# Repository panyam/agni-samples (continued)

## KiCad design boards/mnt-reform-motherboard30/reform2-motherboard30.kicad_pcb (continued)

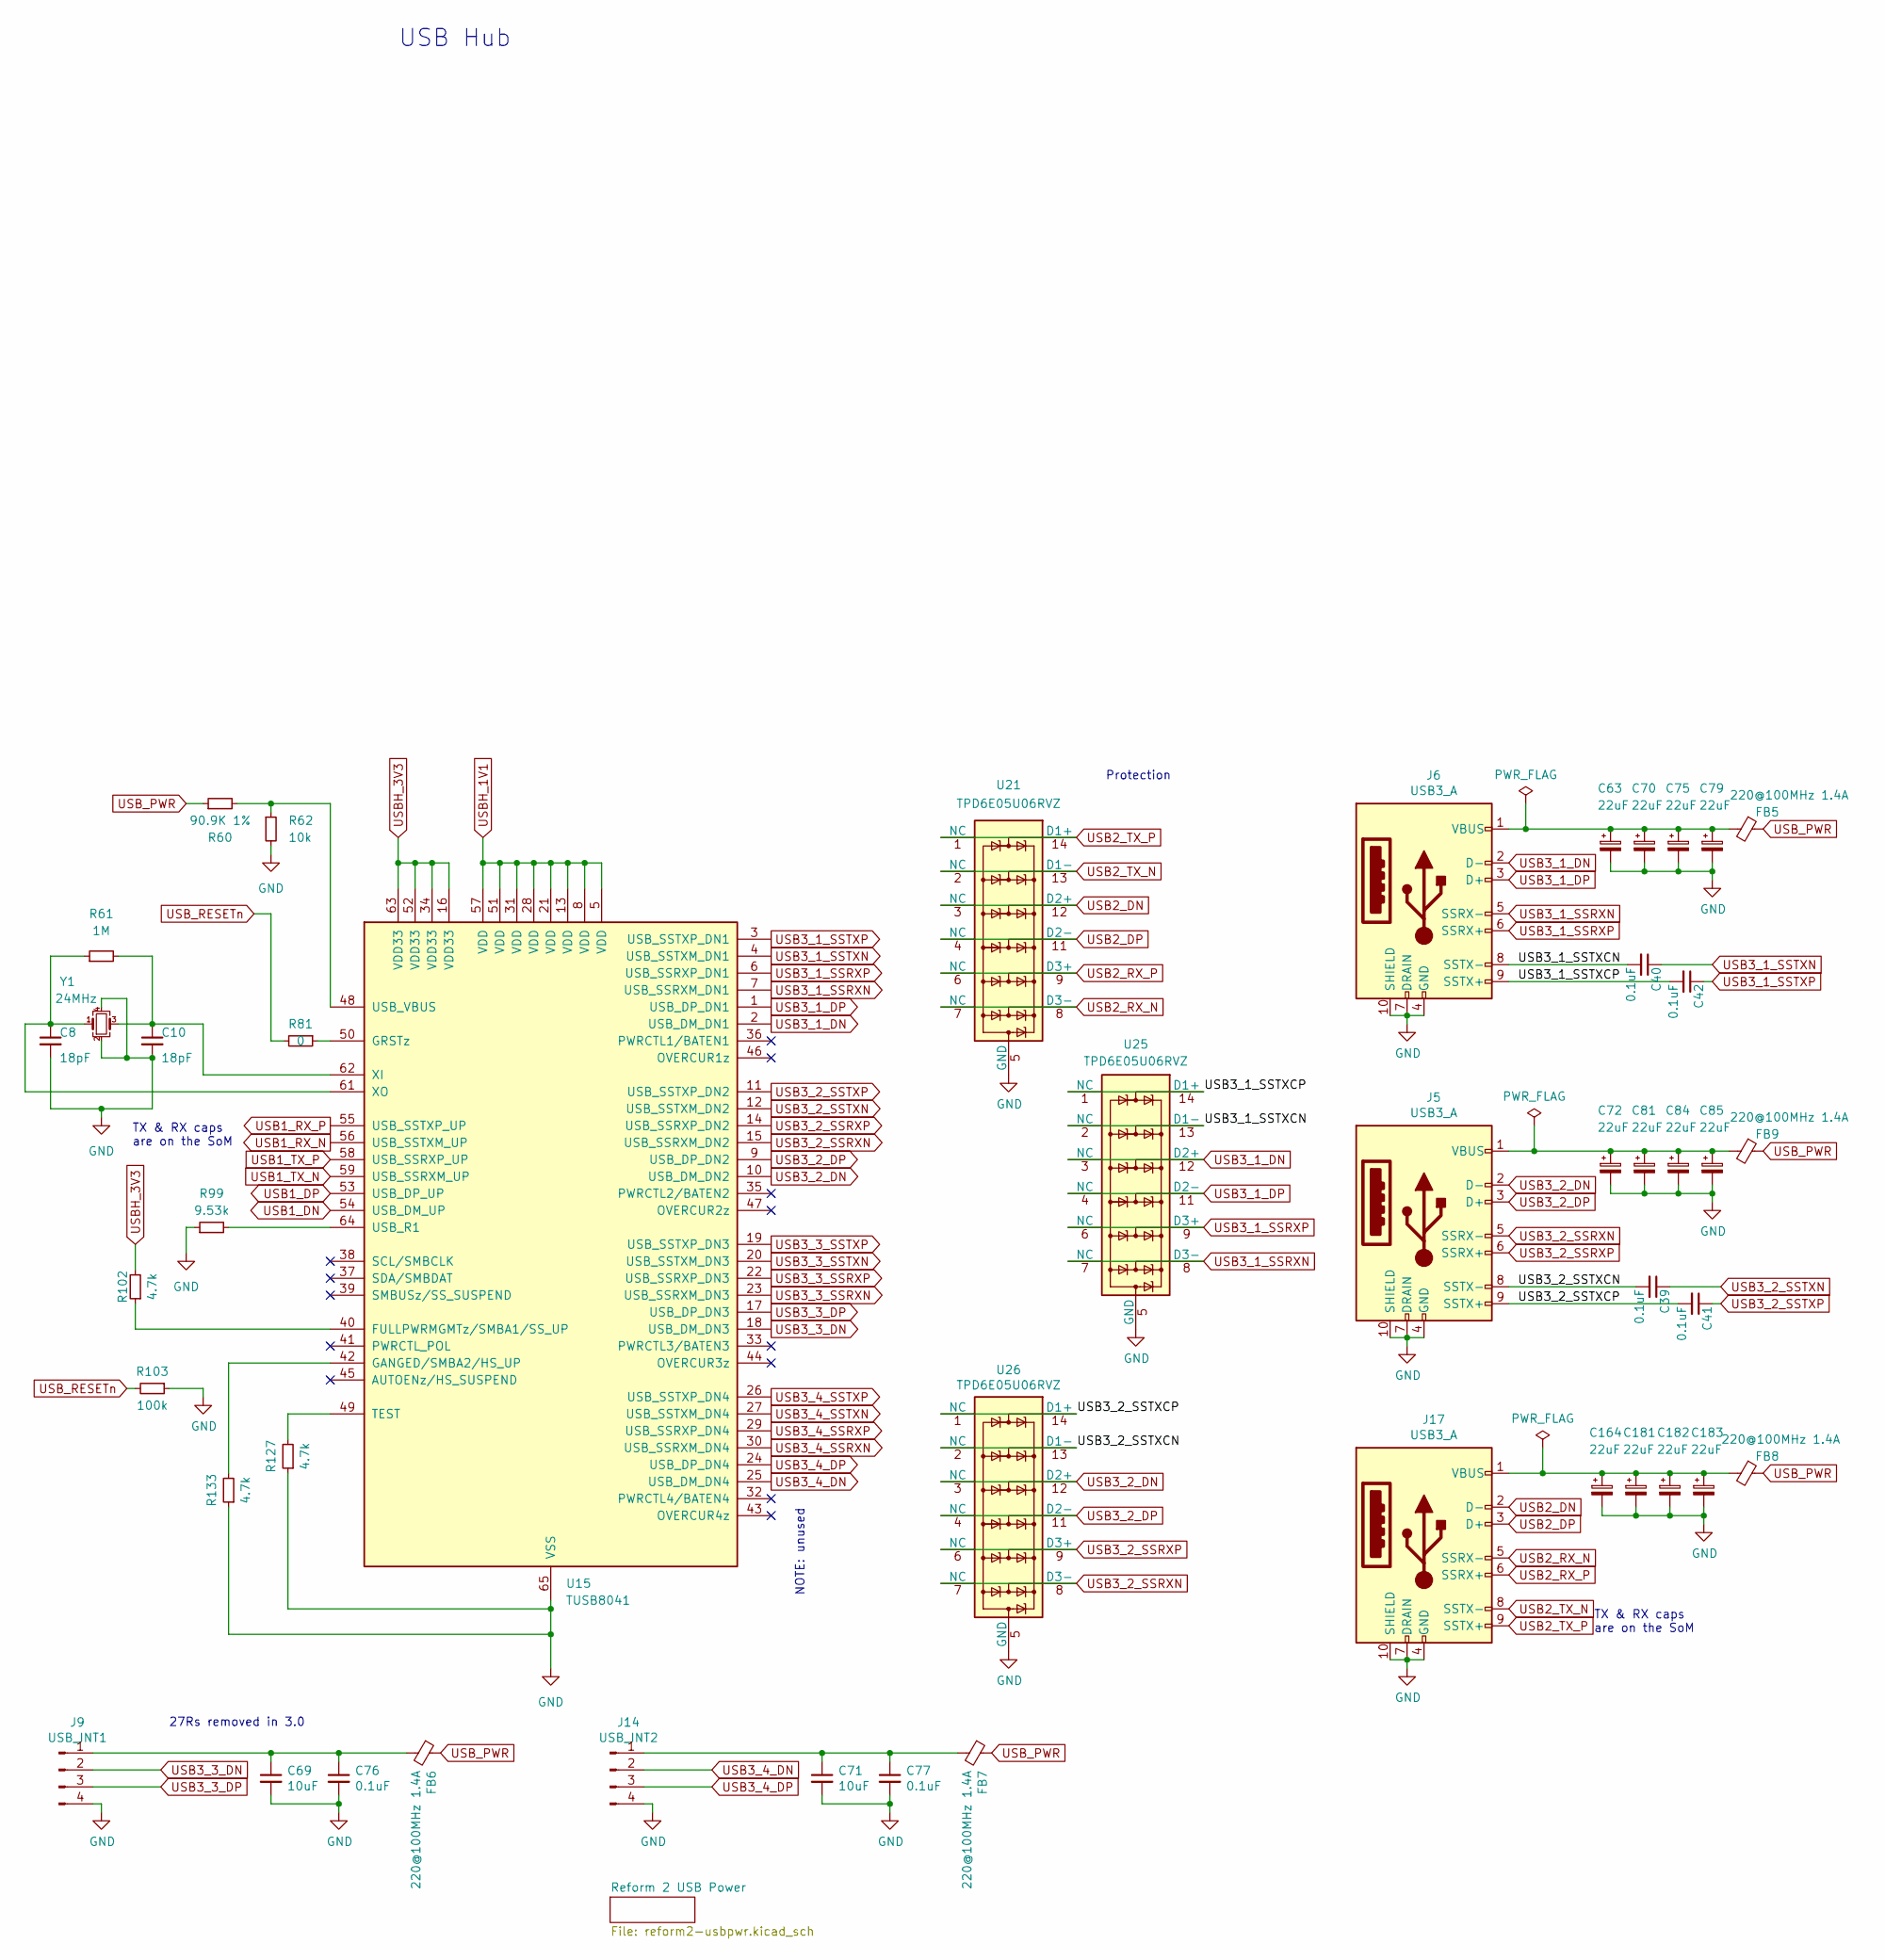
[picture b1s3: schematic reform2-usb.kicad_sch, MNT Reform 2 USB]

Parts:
C8, C10: 18pF; C_0603_1608Metric; LCSC C107040
C39, C40, C41, C42, C76, C77: 0.1uF; C_0603_1608Metric
C63, C70, C72, C75, C79, C81, C84, C85, C164, C181, C182, C183: 22uF; C_0603_1608Metric; LCSC C140782
C69, C71: 10uF; C_0603_1608Metric
FB5, FB6, FB7, FB8, FB9: 220@100MHz 1.4A; L_0603_1608Metric
J5, J6, J17: USB3_A; 692121030100
J9: USB_INT1; JST_PH_B4B-PH-K_1x04_P2.00mm_Vertical
J14: USB_INT2; JST_PH_B4B-PH-K_1x04_P2.00mm_Vertical
R60: 90.9K 1%; R_0603_1608Metric
R61: 1M; R_0603_1608Metric
R62: 10k; R_0603_1608Metric
R81: 0; R_0603_1608Metric
R99: 9.53k; R_0603_1608Metric; LCSC C321660
R102: 4.7k; R_0603_1608Metric; LCSC C105871
R103: 100k; R_0603_1608Metric
R127, R133: 4.7k; R_0603_1608Metric
U15: TUSB8041; QFN-64-1EP_9x9mm_P0.5mm_EP6x6mm_ThermalVias
U21, U25, U26: TPD6E05U06RVZ; Texas_R-PUSON-N14
Y1: 24MHz; Crystal_SMD_Abracon_ABM8G-4Pin_3.2x2.5mm; LCSC C91744

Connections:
/Reform 2 USB/USB3_1_SSTXCN: C40.2, J6.8 (SSTX-), U25.2 (NC), U25.13 (D1-)
/Reform 2 USB/USB3_1_SSTXCP: C42.2, J6.9 (SSTX+), U25.1 (NC), U25.14 (D1+)
/Reform 2 USB/USB3_2_SSTXCN: C39.2, J5.8 (SSTX-), U26.2 (NC), U26.13 (D1-)
/Reform 2 USB/USB3_2_SSTXCP: C41.2, J5.9 (SSTX+), U26.1 (NC), U26.14 (D1+)
GND: C8.2, C10.2, C63.2, C69.2, C70.2, C71.2, C72.2, C75.2, C76.2, C77.2, C79.2, C81.2, C84.2, C85.2, C164.2, C181.2, C182.2, C183.2, J5.4 (GND), J5.7 (DRAIN), J5.10 (SHIELD), J6.4 (GND), J6.7 (DRAIN), J6.10 (SHIELD), J9.4, J14.4, J17.4 (GND), J17.7 (DRAIN), J17.10 (SHIELD), R62.2, R99.1, R103.1, R127.1, R133.1, U15.65 (VSS), U21.5 (GND), U21.10 (GND), U25.5 (GND), U25.10 (GND), U26.5 (GND), U26.10 (GND), Y1.2, Y1.4; also elsewhere on the board
unnamed: C72.1, C81.1, C84.1, C85.1, FB9.2, J5.1 (VBUS)
unnamed: C63.1, C70.1, C75.1, C79.1, FB5.2, J6.1 (VBUS)
unnamed: C69.1, C76.1, FB6.2, J9.1
unnamed: C71.1, C77.1, FB7.2, J14.1
unnamed: C164.1, C181.1, C182.1, C183.1, FB8.2, J17.1 (VBUS)
unnamed: R102.1, U15.40 (FULLPWRMGMTz/SMBA1/SS_UP)
unnamed: R133.2, U15.42 (GANGED/SMBA2/HS_UP)
unnamed: R81.1, U15.50 (GRSTz)
unnamed: R127.2, U15.49 (TEST)
unnamed: R99.2, U15.64 (USB_R1)
unnamed: R60.2, R62.1, U15.48 (USB_VBUS)
unnamed: C10.1, R61.2, U15.62 (XI), Y1.3
unnamed: C8.1, R61.1, U15.61 (XO), Y1.1
USB1_DN: U15.54 (USB_DM_UP); also elsewhere on the board
USB1_DP: U15.53 (USB_DP_UP); also elsewhere on the board
USB1_RX_N: U15.56 (USB_SSTXM_UP); also elsewhere on the board
USB1_RX_P: U15.55 (USB_SSTXP_UP); also elsewhere on the board
USB1_TX_N: U15.59 (USB_SSRXM_UP); also elsewhere on the board
USB1_TX_P: U15.58 (USB_SSRXP_UP); also elsewhere on the board
USB2_DN: J17.2 (D-), U21.3 (NC), U21.12 (D2+); also elsewhere on the board
USB2_DP: J17.3 (D+), U21.4 (NC), U21.11 (D2-); also elsewhere on the board
USB2_RX_N: J17.5 (SSRX-), U21.7 (NC), U21.8 (D3-); also elsewhere on the board
USB2_RX_P: J17.6 (SSRX+), U21.6 (NC), U21.9 (D3+); also elsewhere on the board
USB2_TX_N: J17.8 (SSTX-), U21.2 (NC), U21.13 (D1-); also elsewhere on the board
USB2_TX_P: J17.9 (SSTX+), U21.1 (NC), U21.14 (D1+); also elsewhere on the board
USB3_1_DN: J6.2 (D-), U15.2 (USB_DM_DN1), U25.3 (NC), U25.12 (D2+)
USB3_1_DP: J6.3 (D+), U15.1 (USB_DP_DN1), U25.4 (NC), U25.11 (D2-)
USB3_1_SSRXN: J6.5 (SSRX-), U15.7 (USB_SSRXM_DN1), U25.7 (NC), U25.8 (D3-)
USB3_1_SSRXP: J6.6 (SSRX+), U15.6 (USB_SSRXP_DN1), U25.6 (NC), U25.9 (D3+)
USB3_1_SSTXN: C40.1, U15.4 (USB_SSTXM_DN1)
USB3_1_SSTXP: C42.1, U15.3 (USB_SSTXP_DN1)
USB3_2_DN: J5.2 (D-), U15.10 (USB_DM_DN2), U26.3 (NC), U26.12 (D2+)
USB3_2_DP: J5.3 (D+), U15.9 (USB_DP_DN2), U26.4 (NC), U26.11 (D2-)
USB3_2_SSRXN: J5.5 (SSRX-), U15.15 (USB_SSRXM_DN2), U26.7 (NC), U26.8 (D3-)
USB3_2_SSRXP: J5.6 (SSRX+), U15.14 (USB_SSRXP_DN2), U26.6 (NC), U26.9 (D3+)
USB3_2_SSTXN: C39.1, U15.12 (USB_SSTXM_DN2)
USB3_2_SSTXP: C41.1, U15.11 (USB_SSTXP_DN2)
USB3_3_DN: J9.2, U15.18 (USB_DM_DN3)
USB3_3_DP: J9.3, U15.17 (USB_DP_DN3)
USB3_3_SSRXN: U15.23 (USB_SSRXM_DN3)
USB3_3_SSRXP: U15.22 (USB_SSRXP_DN3)
USB3_3_SSTXN: U15.20 (USB_SSTXM_DN3)
USB3_3_SSTXP: U15.19 (USB_SSTXP_DN3)
USB3_4_DN: J14.2, U15.25 (USB_DM_DN4)
USB3_4_DP: J14.3, U15.24 (USB_DP_DN4)
USB3_4_SSRXN: U15.30 (USB_SSRXM_DN4)
USB3_4_SSRXP: U15.29 (USB_SSRXP_DN4)
USB3_4_SSTXN: U15.27 (USB_SSTXM_DN4)
USB3_4_SSTXP: U15.26 (USB_SSTXP_DN4)
USB_PWR: FB5.1, FB6.1, FB7.1, FB8.1, FB9.1, R60.1; also elsewhere on the board
USB_RESETn: R81.2, R103.2; also elsewhere on the board

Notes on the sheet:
USB Hub
TX & RX caps are on the SoM
NOTE: unused
27Rs removed in 3.0
Protection

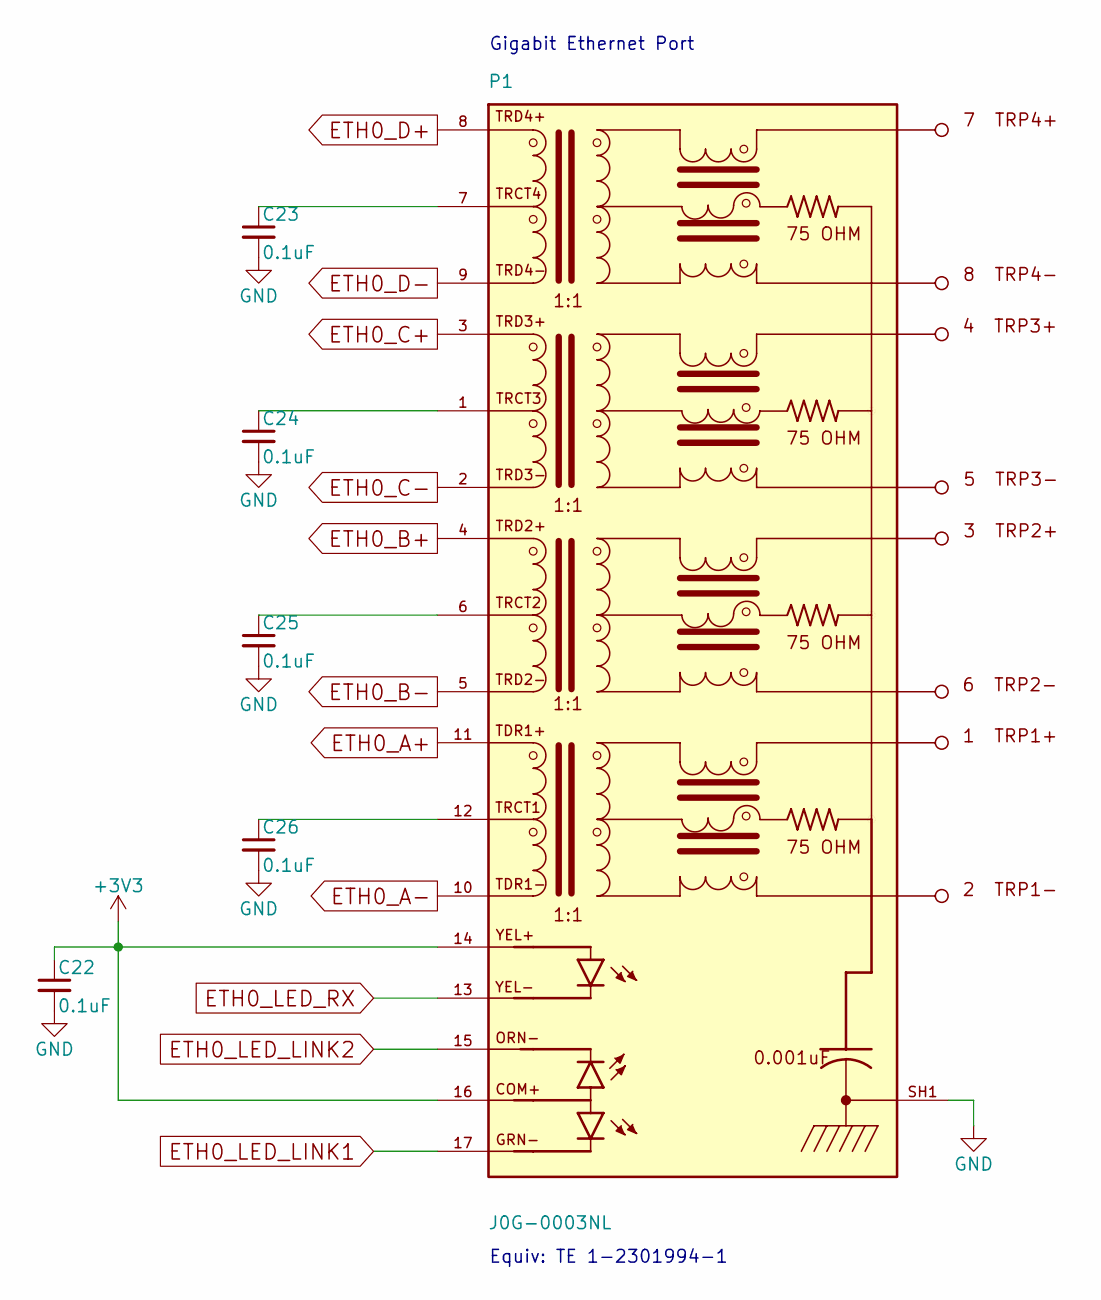
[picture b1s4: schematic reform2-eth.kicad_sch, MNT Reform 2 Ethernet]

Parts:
C22, C23, C24, C25, C26: 0.1uF; C_0603_1608Metric
P1: J0G-0003NL; PULSE_J0G-0003NL

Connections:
+3V3: C22.1, P1.14 (YEL+), P1.16 (COM+); also elsewhere on the board
ETH0_A+: P1.11 (TDR1+); also elsewhere on the board
ETH0_A-: P1.10 (TDR1-); also elsewhere on the board
ETH0_B+: P1.4 (TRD2+); also elsewhere on the board
ETH0_B-: P1.5 (TRD2-); also elsewhere on the board
ETH0_C+: P1.3 (TRD3+); also elsewhere on the board
ETH0_C-: P1.2 (TRD3-); also elsewhere on the board
ETH0_D+: P1.8 (TRD4+); also elsewhere on the board
ETH0_D-: P1.9 (TRD4-); also elsewhere on the board
ETH0_LED_LINK1: P1.17 (GRN-); also elsewhere on the board
ETH0_LED_LINK2: P1.15 (ORN-); also elsewhere on the board
ETH0_LED_RX: P1.13 (YEL-); also elsewhere on the board
GND: C22.2, C23.2, C24.2, C25.2, C26.2, P1.SH1 (SHIELD), P1.SH2 (SHIELD); also elsewhere on the board
unnamed: C26.1, P1.12 (TRCT1)
unnamed: C25.1, P1.6 (TRCT2)
unnamed: C24.1, P1.1 (TRCT3)
unnamed: C23.1, P1.7 (TRCT4)

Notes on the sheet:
Equiv: TE 1-2301994-1
Gigabit Ethernet Port

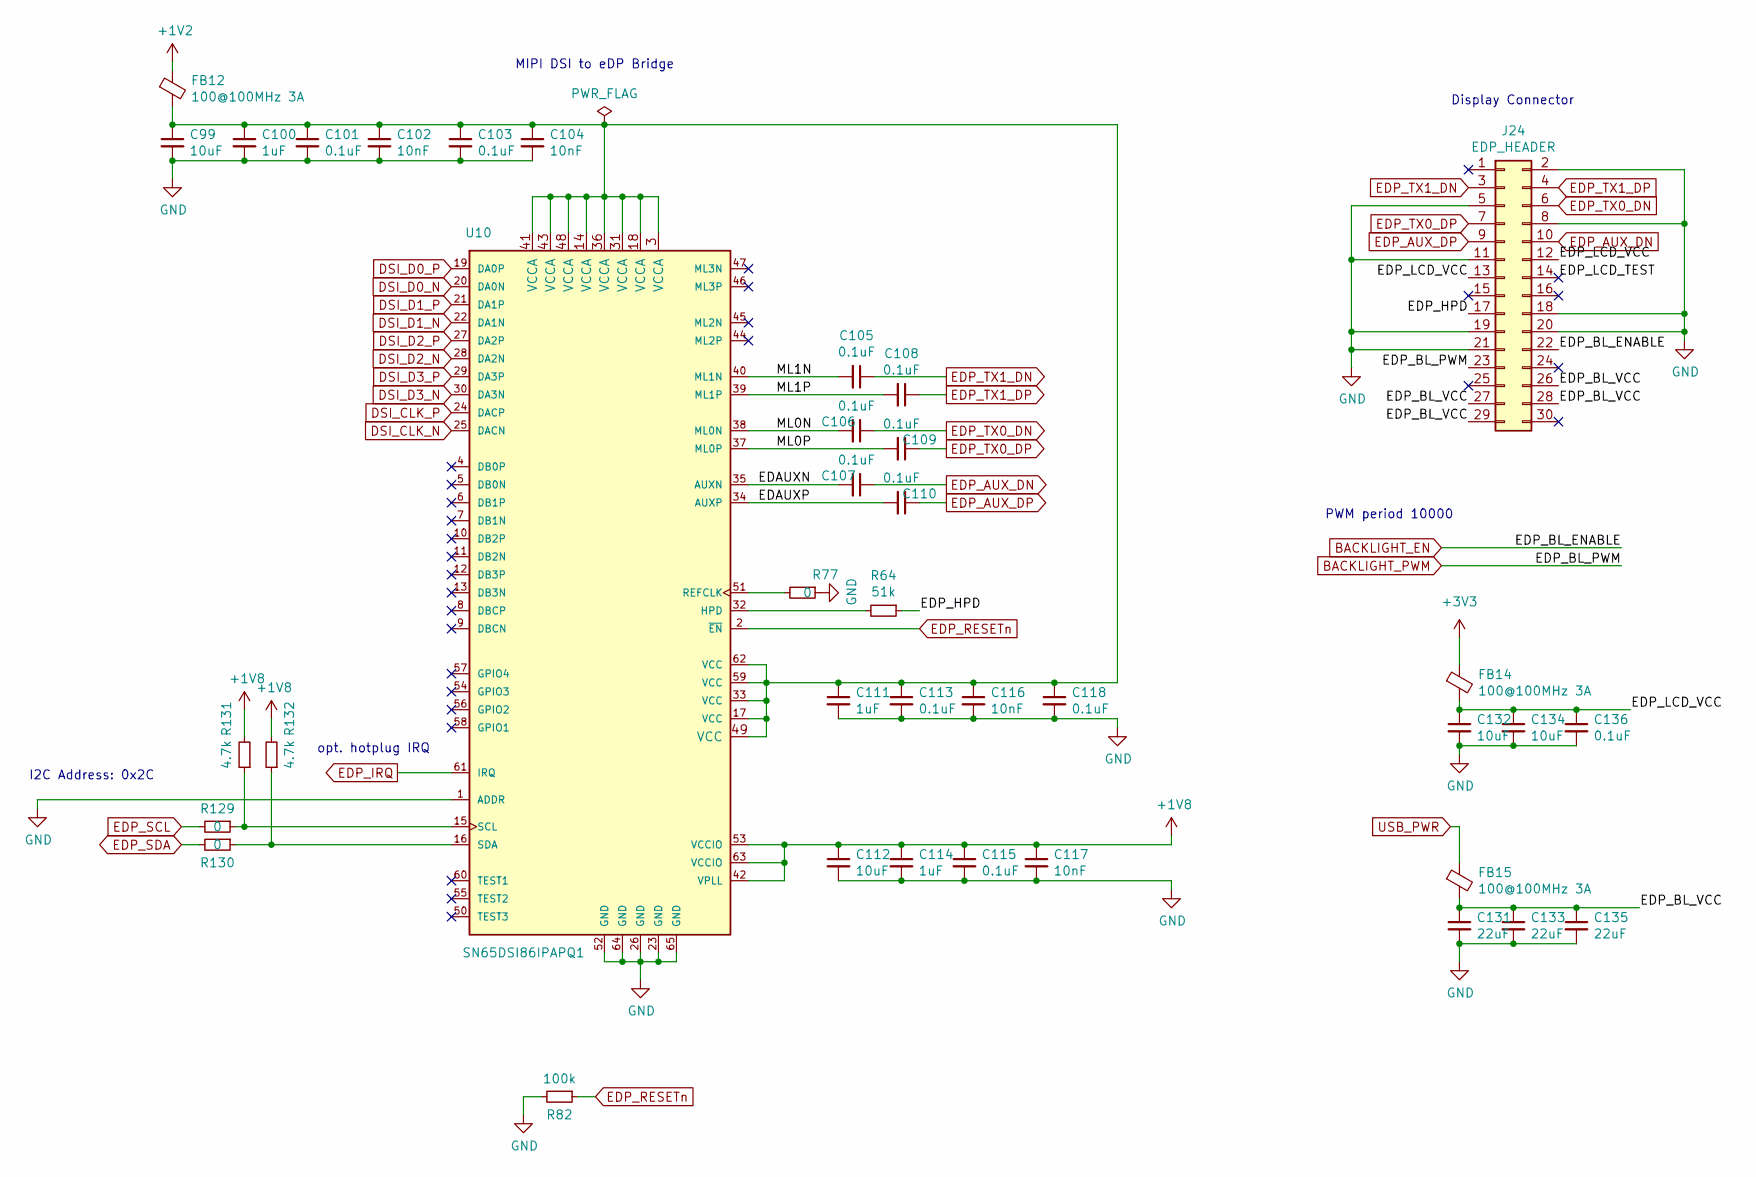
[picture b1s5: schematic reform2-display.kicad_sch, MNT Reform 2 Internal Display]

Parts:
C99, C112, C132, C134: 10uF; C_0603_1608Metric
C100, C111, C114: 1uF; C_0603_1608Metric
C101, C103, C105, C106, C107, C108, C109, C110, C113, C115, C118, C136: 0.1uF; C_0603_1608Metric
C102, C104, C116, C117: 10nF; C_0603_1608Metric
C131, C133, C135: 22uF; C_0603_1608Metric
FB12, FB14, FB15: 100@100MHz 3A; L_0603_1608Metric
J24: EDP_HEADER; PinHeader_2x15_P2.00mm_Vertical
R64: 51k; R_0603_1608Metric
R77, R129, R130: 0; R_0603_1608Metric
R82: 100k; R_0603_1608Metric
R131, R132: 4.7k; R_0603_1608Metric
U10: SN65DSI86IPAPQ1; HTQFP-64-1EP_10x10mm_P0.5mm_EP8x8mm

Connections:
+1V2: FB12.1; also elsewhere on the board
+1V8: C112.1, C114.1, C115.1, C117.1, R131.2, R132.2, U10.42 (VPLL), U10.53 (VCCIO), U10.63 (VCCIO); also elsewhere on the board
+3V3: FB14.1; also elsewhere on the board
/Reform 2 Display/EDAUXN: C107.2, U10.35 (AUXN)
/Reform 2 Display/EDAUXP: C110.2, U10.34 (AUXP)
/Reform 2 Display/EDP_BL_VCC: C131.1, C133.1, C135.1, FB15.2, J24.26, J24.27, J24.28, J24.29
/Reform 2 Display/EDP_HPD: J24.17, R64.1
/Reform 2 Display/EDP_LCD_TEST: J24.14
/Reform 2 Display/EDP_LCD_VCC: C132.1, C134.1, C136.1, FB14.2, J24.12, J24.13
/Reform 2 Display/ML0N: C106.2, U10.38 (ML0N)
/Reform 2 Display/ML0P: C109.2, U10.37 (ML0P)
/Reform 2 Display/ML1N: C105.2, U10.40 (ML1N)
/Reform 2 Display/ML1P: C108.2, U10.39 (ML1P)
BACKLIGHT_EN: J24.22; also elsewhere on the board
BACKLIGHT_PWM: J24.23; also elsewhere on the board
DSI_CLK_N: U10.25 (DACN); also elsewhere on the board
DSI_CLK_P: U10.24 (DACP); also elsewhere on the board
DSI_D0_N: U10.20 (DA0N); also elsewhere on the board
DSI_D0_P: U10.19 (DA0P); also elsewhere on the board
DSI_D1_N: U10.22 (DA1N); also elsewhere on the board
DSI_D1_P: U10.21 (DA1P); also elsewhere on the board
DSI_D2_N: U10.28 (DA2N); also elsewhere on the board
DSI_D2_P: U10.27 (DA2P); also elsewhere on the board
DSI_D3_N: U10.30 (DA3N); also elsewhere on the board
DSI_D3_P: U10.29 (DA3P); also elsewhere on the board
EDP_AUX_DN: C107.1, J24.10
EDP_AUX_DP: C110.1, J24.9
EDP_IRQ: U10.61 (IRQ); also elsewhere on the board
EDP_RESETn: R82.1, U10.2 (~EN); also elsewhere on the board
EDP_SCL: R129.2; also elsewhere on the board
EDP_SDA: R130.2; also elsewhere on the board
EDP_TX0_DN: C106.1, J24.6
EDP_TX0_DP: C109.1, J24.7
EDP_TX1_DN: C105.1, J24.3
EDP_TX1_DP: C108.1, J24.4
GND: C99.2, C100.2, C101.2, C102.2, C103.2, C104.2, C111.2, C112.2, C113.2, C114.2, C115.2, C116.2, C117.2, C118.2, C131.2, C132.2, C133.2, C134.2, C135.2, C136.2, J24.2, J24.5, J24.8, J24.11, J24.18, J24.19, J24.20, J24.21, R77.1, R82.2, U10.1 (ADDR), U10.23 (GND), U10.26 (GND), U10.52 (GND), U10.64 (GND), U10.65 (GND); also elsewhere on the board
unnamed: C99.1, C100.1, C101.1, C102.1, C103.1, C104.1, C111.1, C113.1, C116.1, C118.1, FB12.2, U10.3 (VCCA), U10.14 (VCCA), U10.17 (VCC), U10.18 (VCCA), U10.31 (VCCA), U10.33 (VCC), U10.36 (VCCA), U10.41 (VCCA), U10.43 (VCCA), U10.48 (VCCA), U10.49 (VCC), U10.59 (VCC), U10.62 (VCC)
unnamed: R64.2, U10.32 (HPD)
unnamed: R77.2, U10.51 (REFCLK)
unnamed: R129.1, R131.1, U10.15 (SCL)
unnamed: R130.1, R132.1, U10.16 (SDA)
USB_PWR: FB15.1; also elsewhere on the board

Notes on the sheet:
PWM period 10000
MIPI DSI to eDP Bridge
opt. hotplug IRQ
Display Connector
I2C Address: 0x2C

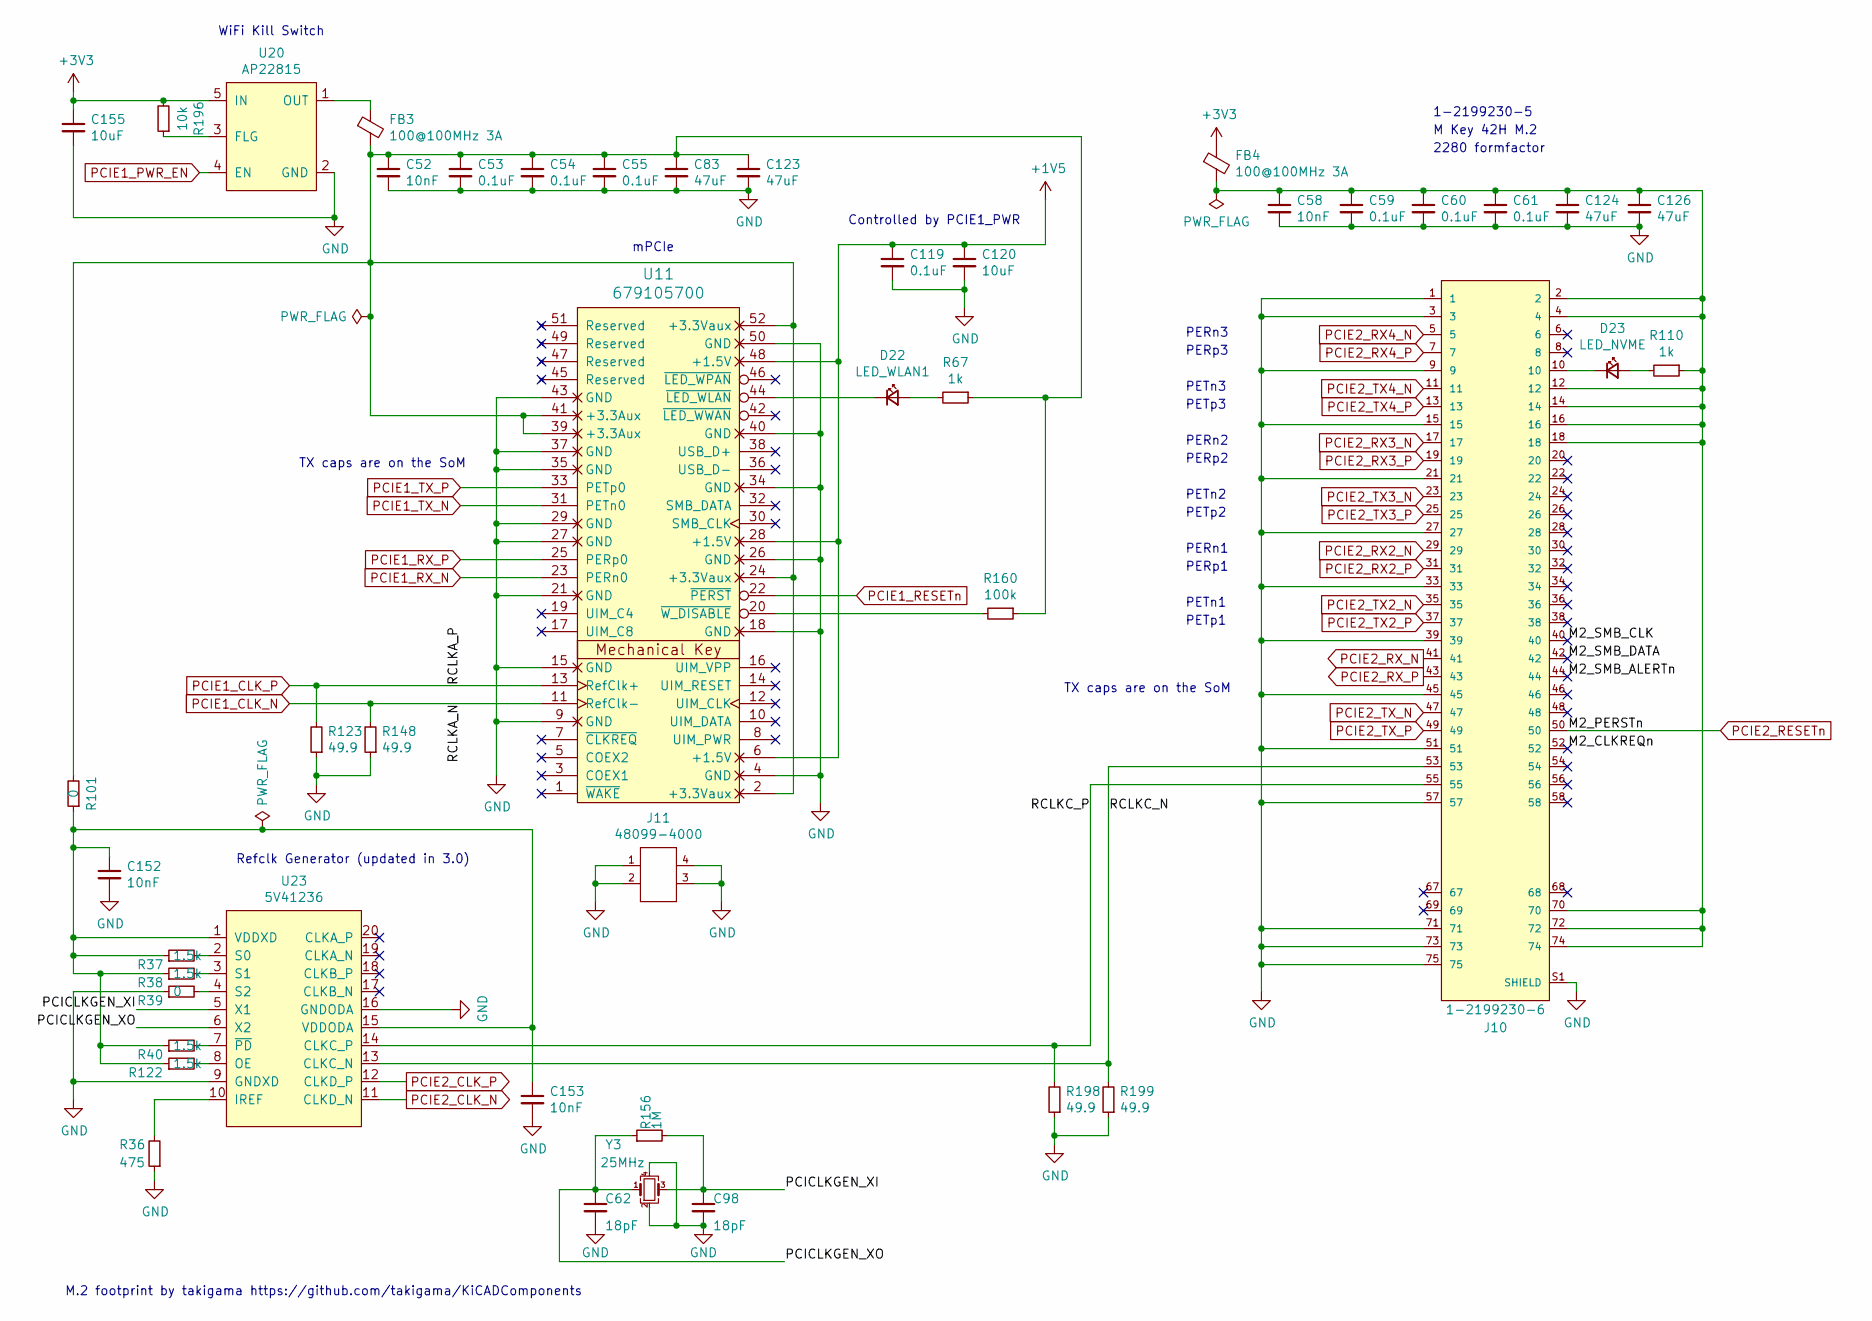
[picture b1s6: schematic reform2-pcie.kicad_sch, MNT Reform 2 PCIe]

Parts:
C52, C58, C152, C153: 10nF; C_0603_1608Metric
C53, C54, C55, C59, C60, C61, C119: 0.1uF; C_0603_1608Metric
C62, C98: 18pF; C_0603_1608Metric; LCSC C107040
C83, C123, C124, C126: 47uF; C_0603_1608Metric
C120, C155: 10uF; C_0603_1608Metric
D22: LED_WLAN1; LED_0603_1608Metric
D23: LED_NVME; LED_0603_1608Metric
FB3, FB4: 100@100MHz 3A; L_0603_1608Metric
J10: 1-2199230-6; TE_1-2199230-6
J11: 48099-4000; MOLEX_48099-5701
R36: 475; R_0603_1608Metric
R37, R38, R40, R122: 1.5k; R_0603_1608Metric
R39, R101: 0; R_0603_1608Metric
R67, R110: 1k; R_0603_1608Metric
R123, R148, R198, R199: 49.9; R_0603_1608Metric
R156: 1M; R_0603_1608Metric
R160: 100k; R_0603_1608Metric
R196: 10k; R_0603_1608Metric
U11: 679105700; MOLEX_67910-5700
U20: AP22815; TSOT-25
U23: 5V41236; TSSOP-20_4.4x6.5mm_P0.65mm
Y3: 25MHz; Crystal_SMD_Abracon_ABM8G-4Pin_3.2x2.5mm

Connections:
+1V5: C119.1, C120.1, U11.6 (+1.5V), U11.28 (+1.5V), U11.48 (+1.5V); also elsewhere on the board
+3V3: C155.1, FB4.1, R196.2, U20.5 (IN); also elsewhere on the board
/Reform 2 PCIe/M2_CLKREQn: J10.52
/Reform 2 PCIe/M2_SMB_ALERTn: J10.44
/Reform 2 PCIe/M2_SMB_CLK: J10.40
/Reform 2 PCIe/M2_SMB_DATA: J10.42
/Reform 2 PCIe/PCICLKGEN_XI: C98.1, R156.2, U23.5 (X1), Y3.3
/Reform 2 PCIe/PCICLKGEN_XO: C62.1, R156.1, U23.6 (X2), Y3.1
/Reform 2 PCIe/RCLKC_N: J10.53, R199.2, U23.13 (CLKC_N)
/Reform 2 PCIe/RCLKC_P: J10.55, R198.2, U23.14 (CLKC_P)
GND: C52.2, C53.2, C54.2, C55.2, C58.2, C59.2, C60.2, C61.2, C62.2, C83.2, C98.2, C119.2, C120.2, C123.2, C124.2, C126.2, C152.2, C153.2, C155.2, J10.1, J10.3, J10.9, J10.15, J10.21, J10.27, J10.33, J10.39, J10.45, J10.51, J10.57, J10.71, J10.73, J10.75, J10.S1 (SHIELD), J10.S2 (SHIELD), J11.1, J11.2, J11.3, J11.4, R36.1, R39.1, R123.1, R148.1, R198.1, R199.1, U11.4 (GND), U11.9 (GND), U11.15 (GND), U11.18 (GND), U11.21 (GND), U11.26 (GND), U11.27 (GND), U11.29 (GND), U11.34 (GND), U11.35 (GND), U11.37 (GND), U11.40 (GND), U11.43 (GND), U11.50 (GND), U20.2 (GND), U23.9 (GNDXD), U23.16 (GNDODA), Y3.2, Y3.4; also elsewhere on the board
unnamed: C52.1, C53.1, C54.1, C55.1, C83.1, C123.1, FB3.2, R67.1, R101.2, R160.1, U11.2 (+3.3Vaux), U11.24 (+3.3Vaux), U11.39 (+3.3Aux), U11.41 (+3.3Aux), U11.52 (+3.3Vaux)
unnamed: C58.1, C59.1, C60.1, C61.1, C124.1, C126.1, FB4.2, J10.2, J10.4, J10.12, J10.14, J10.16, J10.18, J10.70, J10.72, J10.74, R110.1
unnamed: D22.2 (A), R67.2
unnamed: D22.1 (K), U11.44 (~LED_WLAN)
unnamed: D23.2 (A), R110.2
unnamed: D23.1 (K), J10.10
unnamed: R160.2, U11.20 (~W_DISABLE)
unnamed: R196.1, U20.3 (FLG)
unnamed: FB3.1, U20.1 (OUT)
unnamed: R36.2, U23.10 (IREF)
unnamed: R122.2, U23.8 (OE)
unnamed: R37.2, U23.2 (S0)
unnamed: R38.2, U23.3 (S1)
unnamed: R39.2, U23.4 (S2)
unnamed: C152.1, C153.1, R37.1, R38.1, R40.1, R101.1, R122.1, U23.1 (VDDXD), U23.15 (VDDODA)
unnamed: R40.2, U23.7 (~PD)
PCIE1_CLK_N: R148.2, U11.11 (RefClk-); also elsewhere on the board
PCIE1_CLK_P: R123.2, U11.13 (RefClk+); also elsewhere on the board
PCIE1_PWR_EN: U20.4 (EN); also elsewhere on the board
PCIE1_RESETn: U11.22 (~PERST); also elsewhere on the board
PCIE1_RX_N: U11.23 (PERn0); also elsewhere on the board
PCIE1_RX_P: U11.25 (PERp0); also elsewhere on the board
PCIE1_TX_N: U11.31 (PETn0); also elsewhere on the board
PCIE1_TX_P: U11.33 (PETp0); also elsewhere on the board
PCIE2_CLK_N: U23.11 (CLKD_N); also elsewhere on the board
PCIE2_CLK_P: U23.12 (CLKD_P); also elsewhere on the board
PCIE2_RESETn: J10.50; also elsewhere on the board
PCIE2_RX2_N: J10.29; also elsewhere on the board
PCIE2_RX2_P: J10.31; also elsewhere on the board
PCIE2_RX3_N: J10.17; also elsewhere on the board
PCIE2_RX3_P: J10.19; also elsewhere on the board
PCIE2_RX4_N: J10.5; also elsewhere on the board
PCIE2_RX4_P: J10.7; also elsewhere on the board
PCIE2_RX_N: J10.41; also elsewhere on the board
PCIE2_RX_P: J10.43; also elsewhere on the board
PCIE2_TX2_N: J10.35; also elsewhere on the board
PCIE2_TX2_P: J10.37; also elsewhere on the board
PCIE2_TX3_N: J10.23; also elsewhere on the board
PCIE2_TX3_P: J10.25; also elsewhere on the board
PCIE2_TX4_N: J10.11; also elsewhere on the board
PCIE2_TX4_P: J10.13; also elsewhere on the board
PCIE2_TX_N: J10.47; also elsewhere on the board
PCIE2_TX_P: J10.49; also elsewhere on the board

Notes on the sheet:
1-2199230-5
PETn3
Controlled by PCIE1_PWR
PETp1
PERp3
TX caps are on the SoM
PETn2
M.2 footprint by takigama https://github.com/takigama/KiCADComponents
2280 formfactor
Refclk Generator (updated in 3.0)
M Key 42H M.2
PERp2
PERp1
PETp2
mPCIe
PERn3
WiFi Kill Switch
PERn2
PETn1
PERn1
PETp3

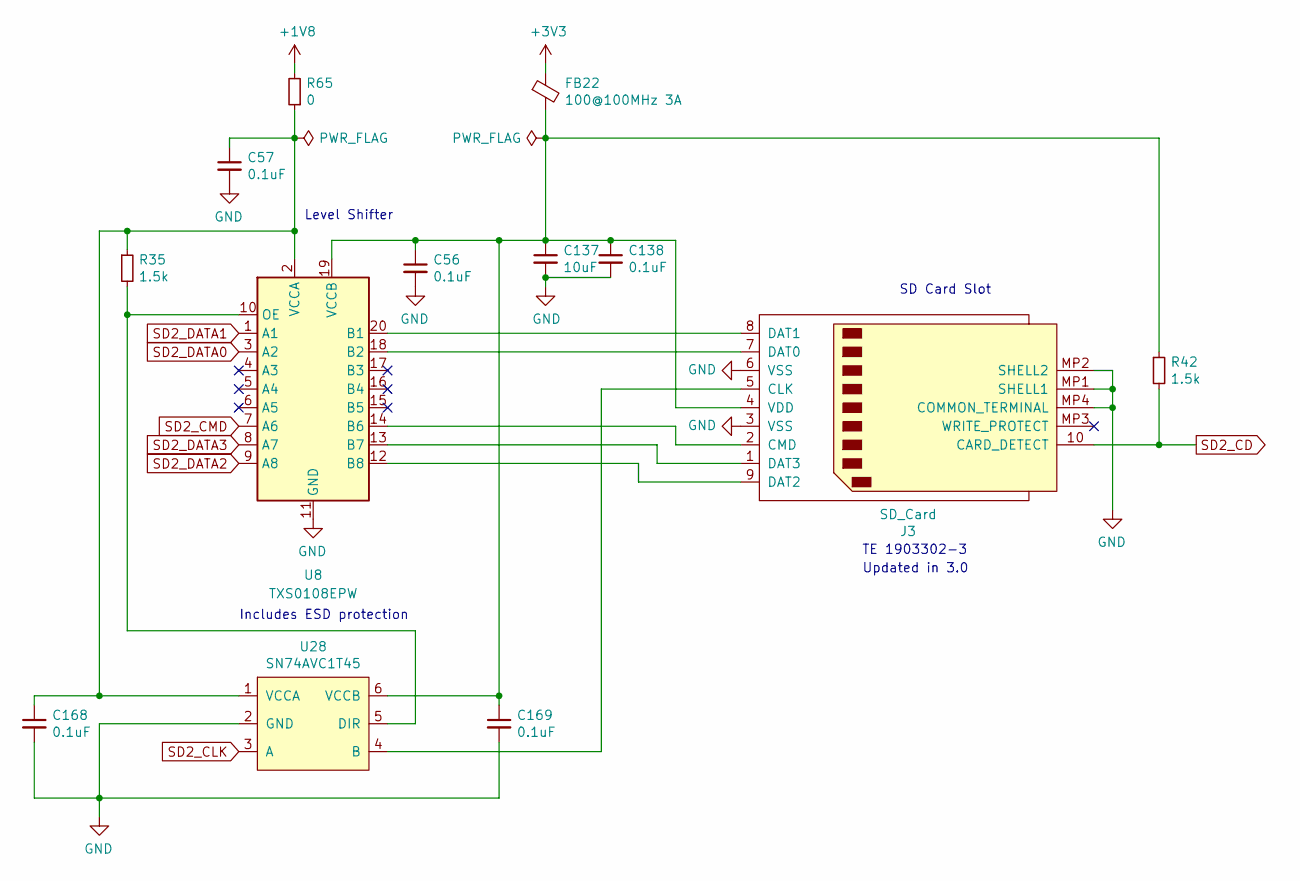
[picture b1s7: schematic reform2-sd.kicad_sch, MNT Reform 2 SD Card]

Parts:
C56, C57, C138, C168, C169: 0.1uF; C_0603_1608Metric
C137: 10uF; C_0603_1608Metric
FB22: 100@100MHz 3A; L_0603_1608Metric
J3: SD_Card; 19033023
R35, R42: 1.5k; R_0603_1608Metric
R65: 0; R_0603_1608Metric
U8: TXS0108EPW; TSSOP-20_4.4x6.5mm_P0.65mm
U28: SN74AVC1T45; SOT-23-6

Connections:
+1V8: R65.2; also elsewhere on the board
+3V3: FB22.1; also elsewhere on the board
GND: C56.2, C57.2, C137.2, C138.2, C168.2, C169.2, J3.3 (VSS), J3.6 (VSS), J3.MP1 (SHELL1), J3.MP2 (SHELL2), J3.MP4 (COMMON_TERMINAL), U8.11 (GND), U28.2 (GND); also elsewhere on the board
unnamed: J3.5 (CLK), U28.4 (B)
unnamed: J3.2 (CMD), U8.14 (B6)
unnamed: J3.7 (DAT0), U8.18 (B2)
unnamed: J3.8 (DAT1), U8.20 (B1)
unnamed: J3.9 (DAT2), U8.12 (B8)
unnamed: J3.1 (DAT3), U8.13 (B7)
unnamed: C56.1, C137.1, C138.1, C169.1, FB22.2, J3.4 (VDD), R42.1, U8.19 (VCCB), U28.6 (VCCB)
unnamed: R35.2, U8.10 (OE), U28.5 (DIR)
unnamed: C57.1, C168.1, R35.1, R65.1, U8.2 (VCCA), U28.1 (VCCA)
SD2_CD: J3.10 (CARD_DETECT), R42.2; also elsewhere on the board
SD2_CLK: U28.3 (A); also elsewhere on the board
SD2_CMD: U8.7 (A6); also elsewhere on the board
SD2_DATA0: U8.3 (A2); also elsewhere on the board
SD2_DATA1: U8.1 (A1); also elsewhere on the board
SD2_DATA2: U8.9 (A8); also elsewhere on the board
SD2_DATA3: U8.8 (A7); also elsewhere on the board

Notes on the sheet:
TE 1903302-3
SD Card Slot
Level Shifter
Includes ESD protection
Updated in 3.0
